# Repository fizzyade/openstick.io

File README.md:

[uri_license]: https://www.gnu.org/licenses/gpl-3.0.en.html
[uri_license_image]: https://img.shields.io/badge/License-GPLv3-blue.svg

[![License: GPLv3][uri_license_image]][uri_license]

# openstick.io
openstick.io is an open source hardware &amp; software project for a USB memory stick.

## About

This project provides an open source hardware design & firmware for a reference implementation of a USB memory stick.  The idea behind this is that extra functionality can be
added to the design, adding encryption, cloning of a stick or more specialised functionality may be added easily.

The actual storage is provided by an on-board Micro SD card, to the host it will look just like a normal memory stick and not a SD card reader.

## Repository Contents

* **/hardware** - KiCad schematic and PCB layout source files.
* **/firmware** - The firmware for the [STM32F070F6Px](https://www.st.com/en/microcontrollers-microprocessors/stm32f070f6.html) microcontroller.

## Required Tools

* **[STM32CubeIDE](https://https://www.st.com/en/development-tools/stm32cubeide.html)** for firmware development.
* **[KiCad](http://kicad-pcb.org/)** for hardware design.

## Project Status

### Hardware

* **Design:** Complete.
* **Manufacture:** In progress.
  * 06-Nov-2019 - PCB's arrived, build and test started.

### Firmware

* **Development:** Started.
  * 06-Nov-2019 - Code based on development board is running correctly, port to actual hardware underway.

## License

This project is open source and the entire project is released under the [GPLv3 license](https://www.gnu.org/licenses/gpl-3.0.en.html).

Distributed as-is; no warranty is given.

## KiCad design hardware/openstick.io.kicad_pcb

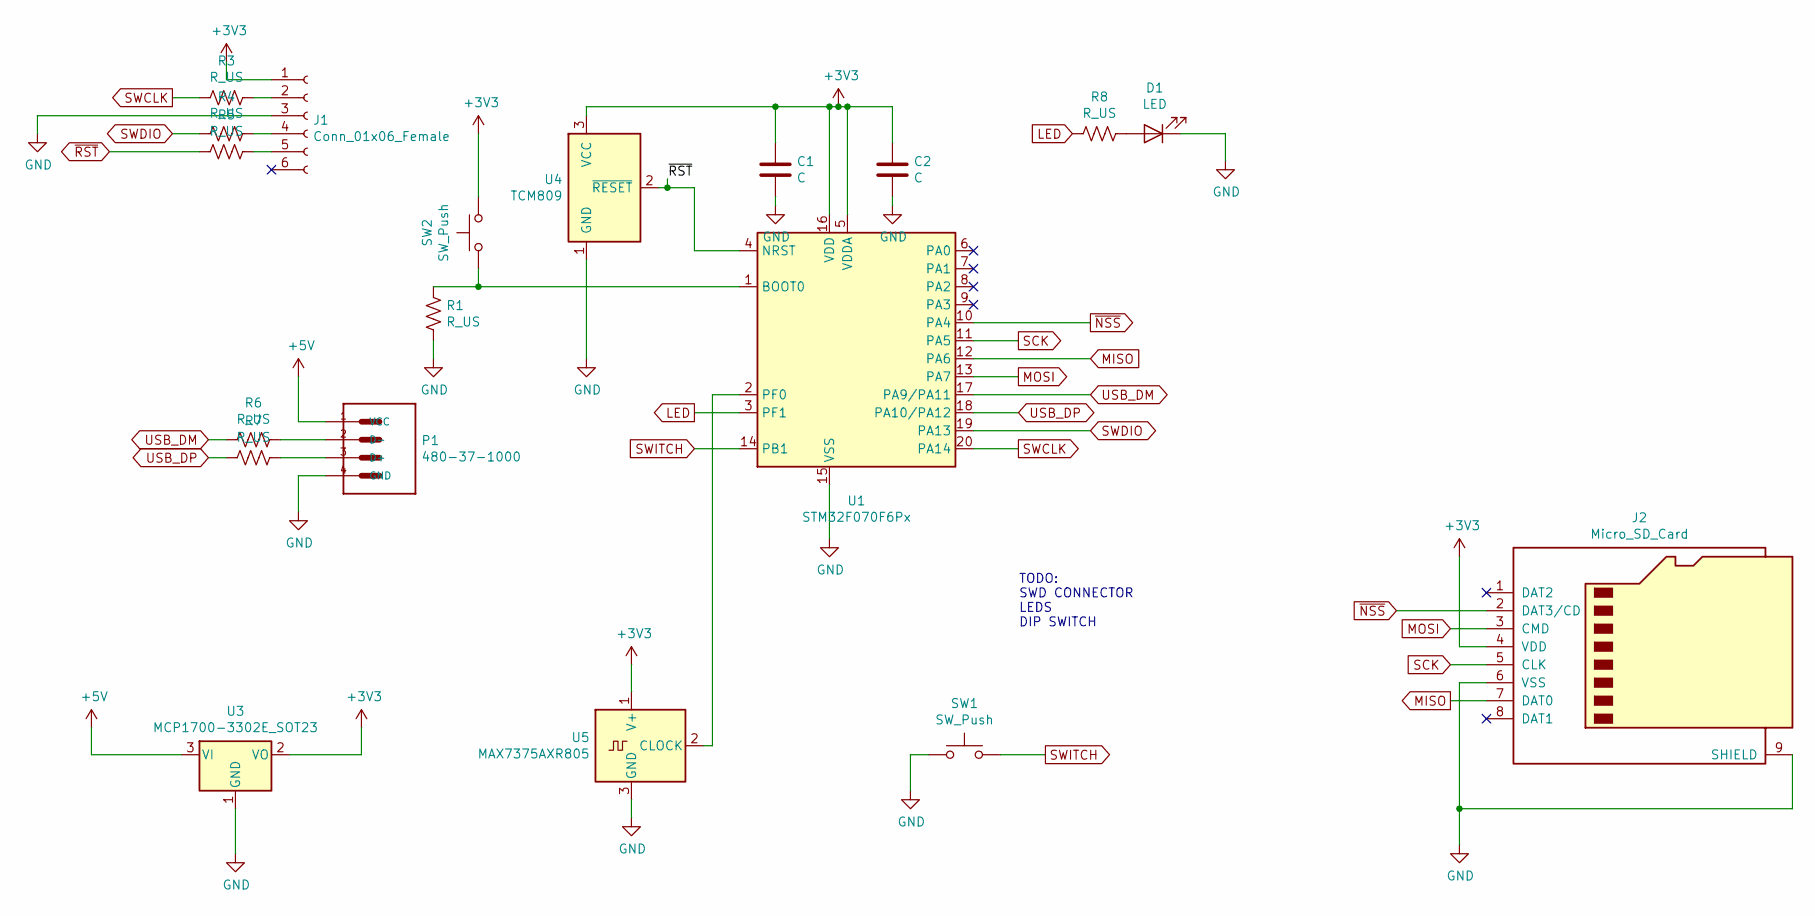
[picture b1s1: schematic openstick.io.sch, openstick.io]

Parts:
C1, C2: C; C_0805_2012Metric_Pad1.15x1.40mm_HandSolder
D1: LED; LED_0805_2012Metric_Pad1.15x1.40mm_HandSolder
J1: Conn_01x06_Female; PinHeader_1x06_P2.54mm_Vertical
J2: Micro_SD_Card; microSD_HC_Hirose_DM3AT-SF-PEJM5
P1: 480-37-1000; MOLEX_480-37-1000
R1, R3, R4, R5, R6, R7, R8: R_US; R_0805_2012Metric_Pad1.15x1.40mm_HandSolder
SW1, SW2: SW_Push; MP000700
U1: STM32F070F6Px; TSSOP-20_4.4x6.5mm_P0.65mm
U3: MCP1700-3302E_SOT23; SOT-23
U4: TCM809; SOT-23
U5: MAX7375AXR805; SOT-323_SC-70

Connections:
+3V3: C1.1, C2.1, J1.1, J2.4 (VDD), SW2.2, U1.5 (VDDA), U1.16 (VDD), U3.2 (VO), U4.3 (VCC), U5.1 (V+); also elsewhere on the board
+5V: P1.1 (VCC), U3.3 (VI)
LED: R8.2, U1.3 (PF1)
MISO: J2.7 (DAT0), U1.12 (PA6)
MOSI: J2.3 (CMD), U1.13 (PA7)
unnamed: D1.2 (A), R8.1
unnamed: J1.2, R3.1
unnamed: J1.4, R4.1
unnamed: J1.5, R5.1
unnamed: P1.2 (D-), R6.1
unnamed: P1.3 (D+), R7.1
unnamed 14: R1.1, SW2.1, U1.1 (BOOT0); also elsewhere on the board
unnamed: U1.2 (PF0), U5.2 (CLOCK)
SCK: J2.5 (CLK), U1.11 (PA5)
SWCLK: R3.2, U1.20 (PA14)
SWDIO: R4.2, U1.19 (PA13)
SWITCH: SW1.2, U1.14 (PB1)
USB_DM: R6.2, U1.17 (PA9/PA11)
USB_DP: R7.2, U1.18 (PA10/PA12)
~NSS: J2.2 (DAT3/CD), U1.10 (PA4)
~RST: R5.2, U1.4 (NRST), U4.2 (~RESET~)

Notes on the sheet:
TODO: SWD CONNECTOR LEDS DIP SWITCH

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
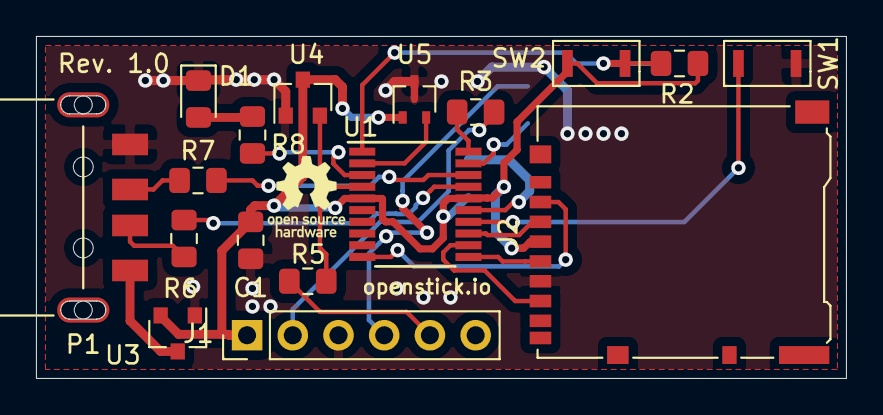
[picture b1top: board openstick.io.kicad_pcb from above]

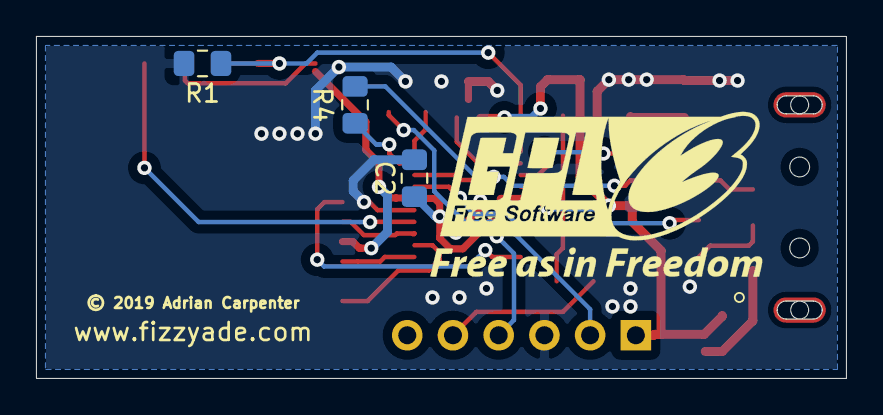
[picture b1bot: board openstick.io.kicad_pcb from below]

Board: 2 copper layers, 45.0 x 19.0 mm, 20 parts (3 on the bottom side), 22 nets.

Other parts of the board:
R2: R_US; R_0805_2012Metric_Pad1.15x1.40mm_HandSolder

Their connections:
+3V3: R2.1; also elsewhere on the board
unnamed 14: R2.2; also elsewhere on the board

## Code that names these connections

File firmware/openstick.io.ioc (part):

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Mcu.Name=STM32F070F6Px
Mcu.Package=TSSOP20
Mcu.UserName=STM32F070F6Px
PA11.Mode=Device
PA11.Signal=USB_DM
PA12.Mode=Device
PA12.Signal=USB_DP
PA13.Mode=Serial_Wire
PA13.Signal=SYS_SWDIO
PA14.Mode=Serial_Wire
PA14.Signal=SYS_SWCLK
PA2.GPIOParameters=GPIO_Label
PA2.GPIO_Label=NRST
PA2.Signal=GPIO_Output
PA4.Mode=NSS_Signal_Hard_Output
PA4.Signal=SPI1_NSS
PA5.Mode=Full_Duplex_Master
PA5.Signal=SPI1_SCK
PA6.Mode=Full_Duplex_Master
PA6.Signal=SPI1_MISO
PA7.Mode=Full_Duplex_Master
PA7.Signal=SPI1_MOSI
PF0-OSC_IN.Mode=HSE-External-Clock-Source
PF0-OSC_IN.Signal=RCC_OSC_IN
PF1-OSC_OUT.GPIOParameters=GPIO_Label
PF1-OSC_OUT.GPIO_Label=LED
PF1-OSC_OUT.Signal=GPIO_Output
RCC.SYSCLKFreq_VALUE=48000000
RCC.SYSCLKSource=RCC_SYSCLKSOURCE_PLLCLK
board=custom

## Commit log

2019-10-09 repo: initial commit
2019-10-09 wip: firmware skeleton created
2019-10-10 repo: switched site theme
2019-10-10 repo: trying another theme
2019-10-10 repo: reverted theme change
2019-10-12 repo: removed tinyusb submodule
2019-11-06 repo: updated README.md

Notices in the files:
hardware/openstick.io.kicad_pcb:
© 2019 Adrian Carpenter
hardware/openstick.io.sch:
Design licensed under the GPL v3 open source license.
